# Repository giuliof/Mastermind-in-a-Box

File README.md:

View this project on [CADLAB.io](https://cadlab.io/project/1102). 

# Mastermind-in-a-Box
A simple Mastermind game with Arduino

## Di cosa si tratta?
È una versione per Arduino del classico gioco del
[Mastermind](https://it.wikipedia.org/wiki/Mastermind).

Il progetto è pensato per essere replicato su BreadBoard, poiché sono
necessari soltanto pochi componenti:
* un display LCD;
* quattro pulsanti;
* quattro resistenze da 10kΩ;
* un buzzer (opzionale)

## Cosa c'è dentro questo repository?
I files sono organizzati come segue:

* `Sorgenti` - il codice sorgente da caricare sulla scheda Arduino. È
dato in due versioni: per montaggio su BreadBoard e per montaggio su PCB.
Fra le due cambia solamente la disposizione di alcuni pin per praticità di collegamento.
* `Circuiti` - ...
 1. Il diagramma delle connessioni su BreadBoard, realizzato con [Fritzing](http://fritzing.org)
 2. Lo schema elettrico, realizzato con [Eagle](http://cadsoft.io)
 3. La PCB
* `Scatola` - il disegno 2D della scatola, intagliabile con una macchina LaserCut (realizzato con [LibreCAD](http://librecad.org))
 
## Istruzioni
on writing...

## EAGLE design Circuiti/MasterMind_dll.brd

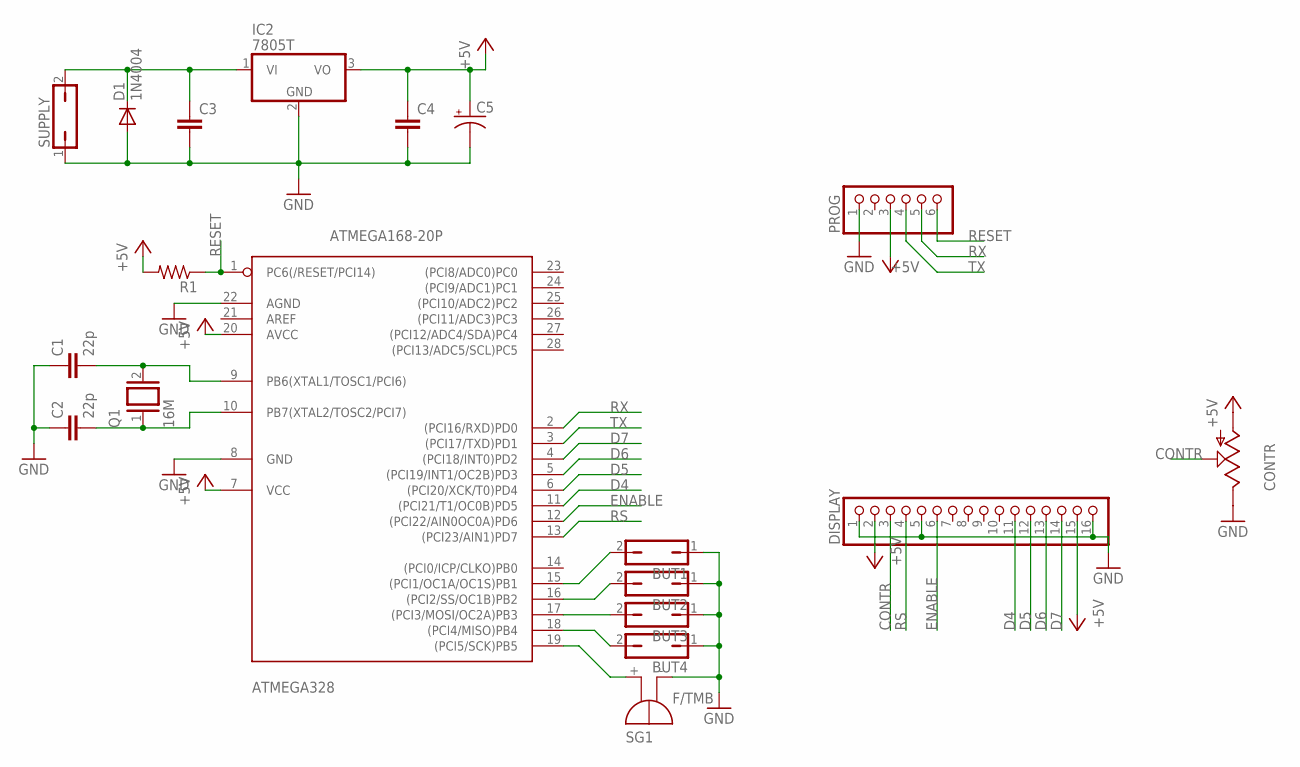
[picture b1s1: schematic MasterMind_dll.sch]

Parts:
ATMEGA328: ATMEGA168-20P; DIL28-3
BUT1, BUT2, BUT3, BUT4: JP1Q; JP1
C1, C2: 22p; C025-024X044
C3, C4: C-EU050-025X075; C050-025X075
C5: CPOL-USE2,5-6E; E2,5-6E
CONTR: TRIM_US-B64Y; B64Y
D1: 1N4004; DO41-10
DISPLAY: PINHD-1X16; 1X16
IC2: 7805T; TO220H
PROG: PINHD-1X6/90; 1X06/90
Q1: 16M; QS
R1: R-US_0204/7; 0204/7
SG1: F/TMB
SUPPLY: JP1Q; JP1

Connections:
+5V: ATMEGA328.7 (VCC), ATMEGA328.20 (AVCC), C4.1, C5.+, CONTR.A, DISPLAY.2, DISPLAY.15, IC2.3 (VO), PROG.3, R1.2; also elsewhere on the board
CONTR: CONTR.S, DISPLAY.3
D4: ATMEGA328.11 ((PCI21/T1/OC0B)PD5), DISPLAY.11
D5: ATMEGA328.6 ((PCI20/XCK/T0)PD4), DISPLAY.12
D6: ATMEGA328.5 ((PCI19/INT1/OC2B)PD3), DISPLAY.13
D7: ATMEGA328.4 ((PCI18/INT0)PD2), DISPLAY.14
ENABLE: ATMEGA328.12 ((PCI22/AIN0OC0A)PD6), DISPLAY.6
GND: ATMEGA328.8 (GND), ATMEGA328.22 (AGND), BUT1.1, BUT2.1, BUT3.1, BUT4.1, C1.1, C2.1, C3.2, C4.2, C5.-, CONTR.E, D1.A, DISPLAY.1, DISPLAY.5, DISPLAY.16, IC2.2 (GND), PROG.1, SG1.-, SUPPLY.1; also elsewhere on the board
unnamed: ATMEGA328.10 (PB7(XTAL2/TOSC2/PCI7)), C2.2, Q1.1
unnamed: ATMEGA328.9 (PB6(XTAL1/TOSC1/PCI6)), C1.2, Q1.2
unnamed: ATMEGA328.19 ((PCI5/SCK)PB5), SG1.+
unnamed: ATMEGA328.18 ((PCI4/MISO)PB4), BUT4.2
unnamed: ATMEGA328.17 ((PCI3/MOSI/OC2A)PB3), BUT3.2
unnamed: ATMEGA328.16 ((PCI2/SS/OC1B)PB2), BUT2.2
unnamed: ATMEGA328.15 ((PCI1/OC1A/OC1S)PB1), BUT1.2
unnamed: C3.1, D1.C, IC2.1 (VI), SUPPLY.2
RESET: ATMEGA328.1 (PC6(/RESET/PCI14)), PROG.6, R1.1; also elsewhere on the board
RS: ATMEGA328.13 ((PCI23/AIN1)PD7), DISPLAY.4
RX: ATMEGA328.3 ((PCI17/TXD)PD1), PROG.4; also elsewhere on the board
TX: ATMEGA328.2 ((PCI16/RXD)PD0), PROG.5; also elsewhere on the board

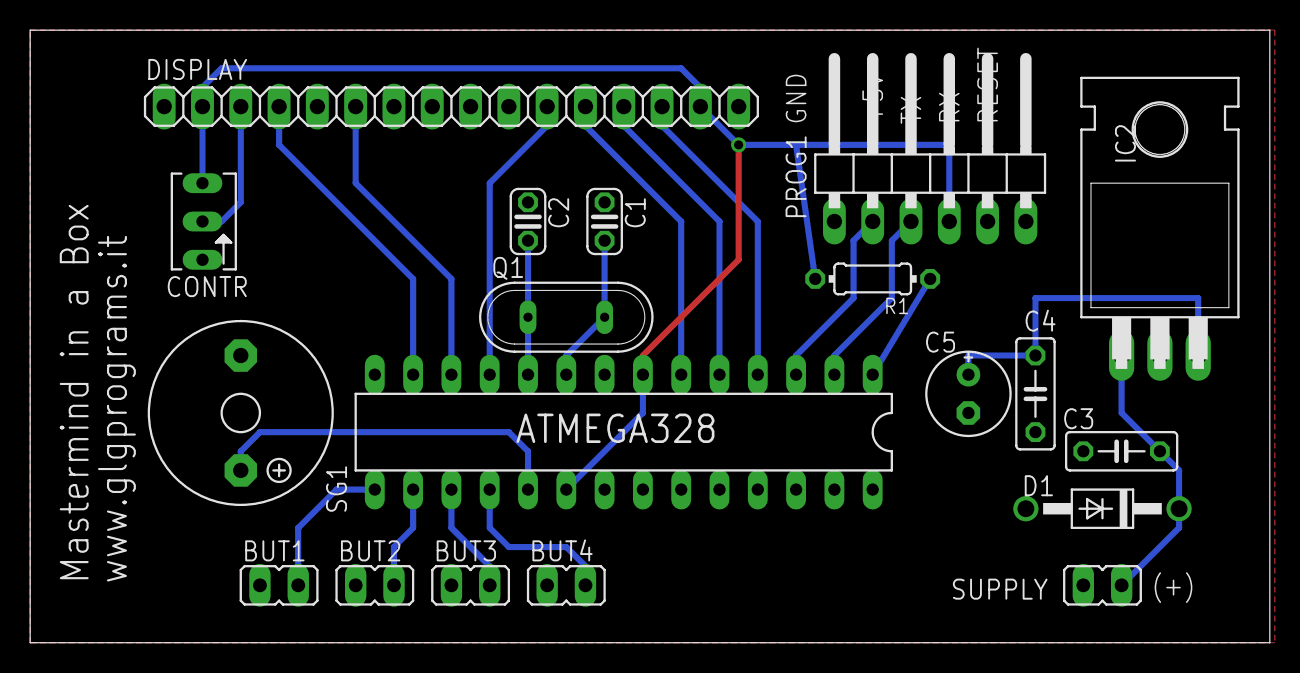
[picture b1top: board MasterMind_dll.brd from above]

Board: 2 copper layers, 82.2 x 40.6 mm, 19 parts (0 on the bottom side), 20 nets.

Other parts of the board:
PROG1: 1X06/90

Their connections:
+5V: PROG1.4; also elsewhere on the board
GND: PROG1.6; also elsewhere on the board
RESET: PROG1.1; also elsewhere on the board
RX: PROG1.2; also elsewhere on the board
TX: PROG1.3; also elsewhere on the board

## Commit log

2016-10-31 Aggiunti circuito, PCB, scatola, sorgente
2016-10-31 Corretto typo, aggiunto schema connessioni
2018-05-26 Backlink to CADLAB.io has been added.
